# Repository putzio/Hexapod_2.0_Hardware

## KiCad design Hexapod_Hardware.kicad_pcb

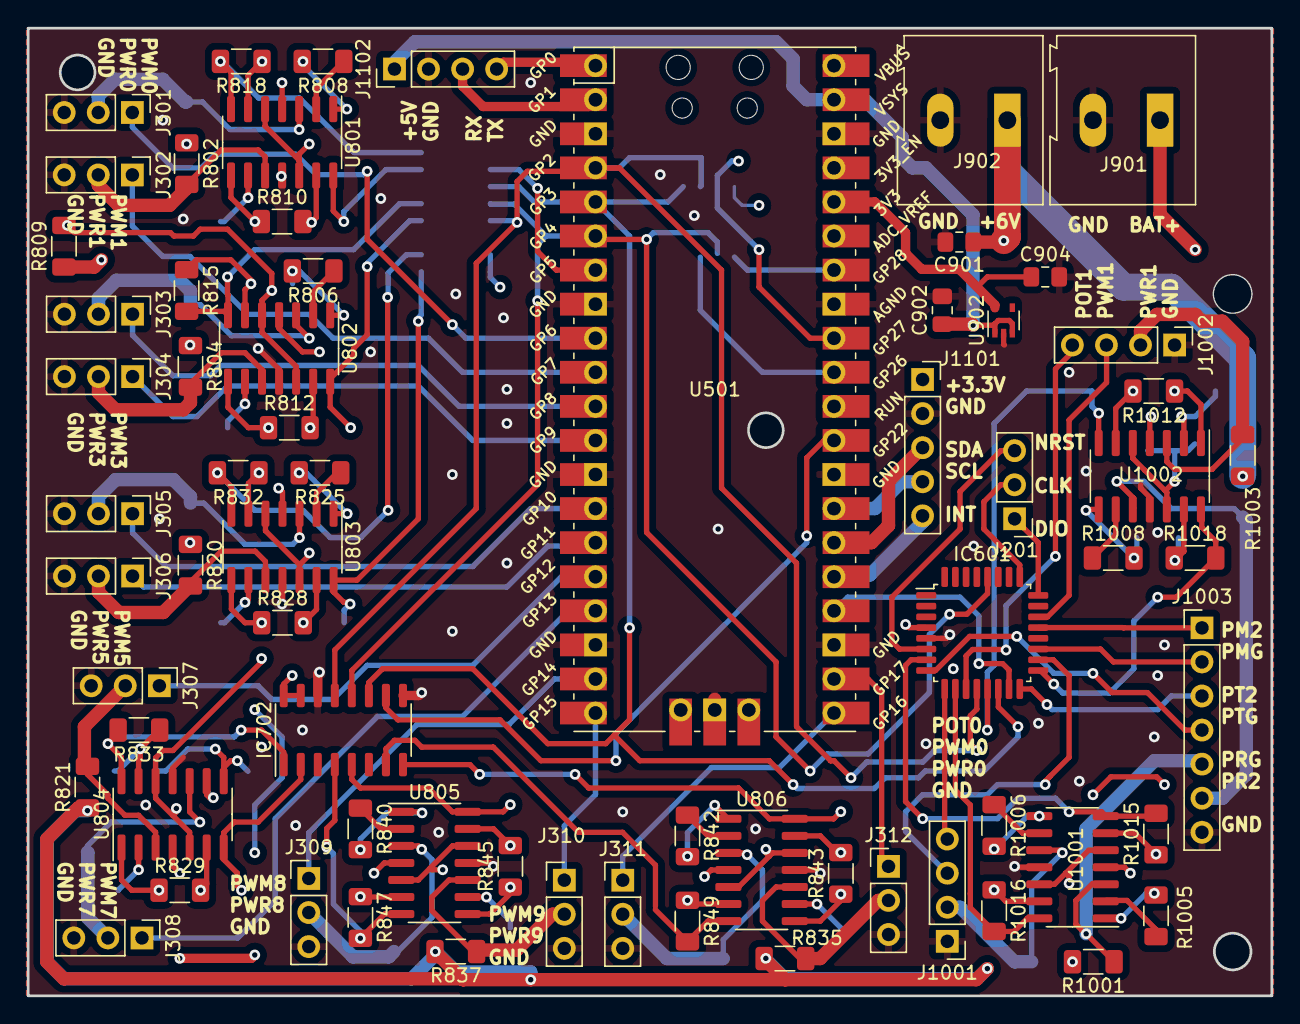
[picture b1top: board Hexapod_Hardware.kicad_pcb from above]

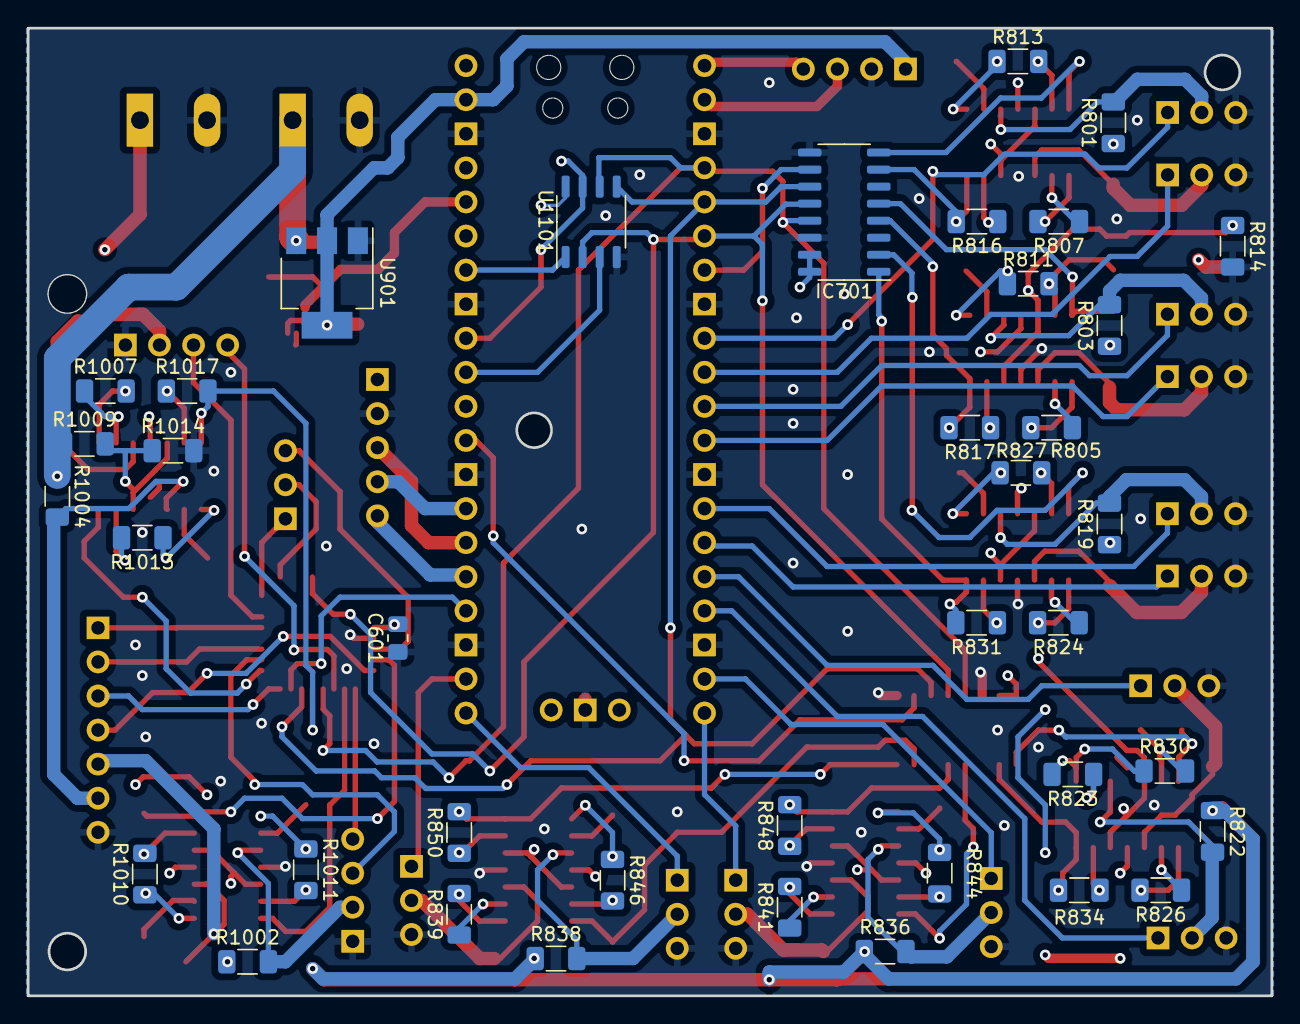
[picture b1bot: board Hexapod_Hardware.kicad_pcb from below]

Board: 4 copper layers, 92.7 x 72.1 mm, 107 parts (39 on the bottom side), 124 nets.

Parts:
C601: 10uF; C_0805_2012Metric_Pad1.18x1.45mm_HandSolder
C901, C902: 22uF; C_0805_2012Metric_Pad1.18x1.45mm_HandSolder
C904: 1uF; C_0805_2012Metric_Pad1.18x1.45mm_HandSolder
IC601: STM32G030K8T6; LQFP-32_7x7mm_P0.8mm
IC701, IC702: MCP3008-I_SL; SO-16_3.9x9.9mm_P1.27mm
J201: Conn_01x03; PinHeader_1x03_P2.54mm_Vertical
J301, J302, J303, J304, J305, J306, J307, J308, J309, J310, J311, J312: Conn_01x03_Female; PinHeader_1x03_P2.54mm_Vertical
J901, J902: Screw_Terminal_01x02; TerminalBlock_Altech_AK300-2_P5.00mm
J1001, J1002: Conn_01x04_Pin; PinHeader_1x04_P2.54mm_Vertical
J1003: Conn_01x07; PinHeader_1x07_P2.54mm_Vertical
J1101: Conn_01x05_Pin; PinSocket_1x05_P2.54mm_Vertical
J1102: Conn_01x04_Socket; PinHeader_1x04_P2.54mm_Vertical
R801: 0R39; R_1206_3216Metric_Pad1.30x1.75mm_HandSolder
R802, R803, R804, R805, R806, R807, R808, R819, R820, R821, R822, R823, R824, R825, R826, R835, R836, R837, R838, R839, R840, R842, R1001, R1002, R1003, R1004, R1005, R1006, R1007, R1008: R; R_1206_3216Metric_Pad1.30x1.75mm_HandSolder
R809, R810, R811, R812, R813, R827, R828, R829, R830, R843, R844, R845, R846, R1009, R1010, R1011, R1012, R1013: 10k; R_1206_3216Metric_Pad1.30x1.75mm_HandSolder
R814, R815, R816, R817, R818, R831, R832, R833, R834, R841, R847, R848, R849, R850, R1014, R1015, R1016, R1017, R1018: 47k; R_1206_3216Metric_Pad1.30x1.75mm_HandSolder
U501: Pico; RPi_Pico_SMD_TH
U801, U802, U803, U804, U805, U806, U1001, U1002: LM2902; SOIC-14_3.9x8.7mm_P1.27mm
U901: AZ1117CH-5.0TRG1; SOT-223-3_TabPin2
U902: LD29150DT33R; SOT-353_SC-70-5
U1101: AT25SF081-XMHD-X; SOP-8_3.9x4.9mm_P1.27mm

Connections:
+3.3V: C601.2, C904.1, IC601.4 (VDD/VDDA), IC701.15 (VREF), IC701.16 (VDD), IC702.15 (VREF), IC702.16 (VDD), J1101.1, U501.36 (3V3), U902.5 (VOUT), U1101.8 (VCC)
+5V: C902.1, J1102.1, U501.39 (VSYS), U901.2 (VO), U902.1 (VIN), U902.3 (EN)
+6V: C901.1, J902.1, R801.1, R802.1, R803.1, R804.1, R809.1, R819.1, R820.1, R821.1, R822.1, R835.1, R836.1, R837.1, R838.1, R1001.1, R1002.1, R1003.1, R1004.1, R1009.1, U901.3 (VI)
+8V: J901.1, U801.4 (V+), U802.4 (V+), U803.4 (V+), U804.4 (V+), U805.4 (V+), U806.4 (V+), U1001.4 (V+), U1002.4 (V+)
/MCU/FLASH_HOLD: U501.32 (GPIO27_ADC1), U1101.7 (~HOLD/IO3)
/MCU/FLASH_WP: U501.31 (GPIO26_ADC0), U1101.3 (~WP/IO2)
/MCU/I2C_SCL: J1101.4, U501.27 (GPIO21)
/MCU/I2C_SDA: J1101.3, U501.26 (GPIO20)
/MCU/MPU6050_INT: J1101.5, U501.25 (GPIO19)
/MCU/RX: J1102.3, U501.2 (GPIO1)
/MCU/SERVO_0: J301.1, U501.9 (GPIO6)
/MCU/SERVO_1: J302.1, U501.10 (GPIO7)
/MCU/SERVO_2: J303.1, U501.11 (GPIO8)
/MCU/SERVO_3: J304.1, U501.12 (GPIO9)
/MCU/SERVO_4: J305.1, U501.14 (GPIO10)
/MCU/SERVO_5: J306.1, U501.15 (GPIO11)
/MCU/SERVO_6: J307.1, U501.16 (GPIO12)
/MCU/SERVO_7: J308.1, U501.17 (GPIO13)
/MCU/SERVO_8: J309.1, U501.19 (GPIO14)
/MCU/SERVO_9: J310.1, U501.20 (GPIO15)
/MCU/SERVO_10: J311.1, U501.21 (GPIO16)
/MCU/SERVO_11: J312.1, U501.22 (GPIO17)
/MCU/SPI_CLK: IC601.12 (PA5), IC701.13 (CLK), IC702.13 (CLK), U501.4 (GPIO2), U1101.6 (SCK)
/MCU/SPI_CS_0: IC701.10 (~CS/SHDN), U501.7 (GPIO5)
/MCU/SPI_CS_1: IC702.10 (~CS/SHDN), U501.29 (GPIO22)
/MCU/SPI_CS_2: U501.34 (GPIO28_ADC2), U1101.1 (~CS)
/MCU/SPI_CS_GRIPPER: IC601.15 (PB0), U501.24 (GPIO18)
/MCU/SPI_MISO: IC601.28 (PB4), IC701.12 (DOUT), IC702.12 (DOUT), U501.6 (GPIO4), U1101.2 (SO/IO1)
/MCU/SPI_MOSI: IC601.14 (PA7), IC701.11 (DIN), IC702.11 (DIN), U501.5 (GPIO3), U1101.5 (SI/IO0)
/MCU/TX: J1102.4, U501.1 (GPIO0)
/SERVO + ADC/ADC/CURRENT_SENSOR_0: IC701.8 (CH7), R818.2, U801.7
/SERVO + ADC/ADC/CURRENT_SENSOR_1: IC701.7 (CH6), R816.2, U801.14
/SERVO + ADC/ADC/CURRENT_SENSOR_2: IC701.5 (CH4), R815.2, U802.7
/SERVO + ADC/ADC/CURRENT_SENSOR_3: IC701.4 (CH3), R817.2, U802.14
/SERVO + ADC/ADC/CURRENT_SENSOR_4: IC701.2 (CH1), R832.2, U803.7
/SERVO + ADC/ADC/CURRENT_SENSOR_5: IC701.1 (CH0), R831.2, U803.14
/SERVO + ADC/ADC/CURRENT_SENSOR_6: IC702.2 (CH1), R834.2, U804.7
/SERVO + ADC/ADC/CURRENT_SENSOR_7: IC702.1 (CH0), R833.2, U804.14
/SERVO + ADC/ADC/CURRENT_SENSOR_8: IC702.4 (CH3), R847.2, U805.7
/SERVO + ADC/ADC/CURRENT_SENSOR_9: IC702.5 (CH4), R848.2, U805.14
/SERVO + ADC/ADC/CURRENT_SENSOR_10: IC702.7 (CH6), R849.2, U806.7
/SERVO + ADC/ADC/CURRENT_SENSOR_11: IC702.8 (CH7), R850.2, U806.14
/SERVO + ADC/Current Sensors/SERVO_PWR_0: J301.2, R801.2, U801.3 (+)
/SERVO + ADC/Current Sensors/SERVO_PWR_1: J302.2, R802.2, U801.10 (+)
/SERVO + ADC/Current Sensors/SERVO_PWR_2: J303.2, R803.2, U802.3 (+)
/SERVO + ADC/Current Sensors/SERVO_PWR_3: J304.2, R804.2, U802.10 (+)
/SERVO + ADC/Current Sensors/SERVO_PWR_4: J305.2, R819.2, U803.3 (+)
/SERVO + ADC/Current Sensors/SERVO_PWR_5: J306.2, R820.2, U803.10 (+)
/SERVO + ADC/Current Sensors/SERVO_PWR_6: J307.2, R821.2, U804.3 (+)
/SERVO + ADC/Current Sensors/SERVO_PWR_7: J308.2, R822.2, U804.10 (+)
/SERVO + ADC/Current Sensors/SERVO_PWR_8: J309.2, R836.2, U805.3 (+)
/SERVO + ADC/Current Sensors/SERVO_PWR_9: J310.2, R837.2, U805.10 (+)
/SERVO + ADC/Current Sensors/SERVO_PWR_10: J311.2, R838.2, U806.3 (+)
/SERVO + ADC/Current Sensors/SERVO_PWR_11: J312.2, R835.2, U806.10 (+)
/SERVO + ADC/Current Sensors/V_BAT_REF: R809.2, R814.1, U801.5 (+), U801.12 (+), U802.5 (+), U802.12 (+), U803.5 (+), U803.12 (+), U804.5 (+), U804.12 (+), U805.5 (+), U805.12 (+), U806.5 (+), U806.12 (+)
/SUPPORTING_MODULES/Gripper/Gripper_servo/SERVO_0_CURRENT: IC601.10 (PA3), R1016.2, U1001.14
/SUPPORTING_MODULES/Gripper/Gripper_servo/SERVO_1_CURRENT: IC601.13 (PA6), R1017.2, U1002.7
/SUPPORTING_MODULES/Gripper/Gripper_servo/SERVO_2_CURRENT: IC601.17 (PB2), R1018.2, U1002.14
/SUPPORTING_MODULES/Gripper/Gripper_servo/SERVO_CURRENT_GRIPPER: IC601.7 (PA0), R1015.2, U1001.7
/SUPPORTING_MODULES/Gripper/Gripper_servo/SERVO_POTENTIOMETER_0: IC601.9 (PA2), J1001.4
/SUPPORTING_MODULES/Gripper/Gripper_servo/SERVO_POTENTIOMETER_1: IC601.11 (PA4), J1002.4
/SUPPORTING_MODULES/Gripper/Gripper_servo/SERVO_POTENTIOMETER_2: IC601.16 (PB1), J1003.3
/SUPPORTING_MODULES/Gripper/Gripper_servo/SERVO_POTENTIOMETER_GRIPPER: IC601.8 (PA1), J1003.4
/SUPPORTING_MODULES/Gripper/Gripper_servo/SERVO_PWM_0: IC601.18 (PA8), J1001.3
/SUPPORTING_MODULES/Gripper/Gripper_servo/SERVO_PWM_1: IC601.22 (PA11_[PA9]), J1002.3
/SUPPORTING_MODULES/Gripper/Gripper_servo/SERVO_PWM_2: IC601.21 (PA10), J1003.1
/SUPPORTING_MODULES/Gripper/Gripper_servo/SERVO_PWM_GRIPPER: IC601.19 (PA9), J1003.2
/SUPPORTING_MODULES/Gripper/Gripper_servo/SERVO_PWR_0: J1001.2, R1002.2, U1001.10 (+)
/SUPPORTING_MODULES/Gripper/Gripper_servo/SERVO_PWR_1: J1002.2, R1003.2, U1002.3 (+)
/SUPPORTING_MODULES/Gripper/Gripper_servo/SERVO_PWR_2: J1003.6, R1004.2, U1002.10 (+)
/SUPPORTING_MODULES/Gripper/Gripper_servo/SERVO_PWR_GRIPPER: J1003.5, R1001.2, U1001.3 (+)
/SUPPORTING_MODULES/Gripper/Gripper_servo/V_BAT_REF: R1009.2, R1014.1, U1001.5 (+), U1001.12 (+), U1002.5 (+), U1002.12 (+)
/SUPPORTING_MODULES/Gripper/MCU_GRIPPER/NRST: IC601.6 (NRST), J201.3
/SUPPORTING_MODULES/Gripper/MCU_GRIPPER/SWCLK: IC601.25 (PA14-BOOT0), J201.2
/SUPPORTING_MODULES/Gripper/MCU_GRIPPER/SWDIO: IC601.24 (PA13), J201.1
GND: C601.1, C901.2, C902.2, C904.2, IC601.5 (VSS/VSSA), IC701.9 (DGND), IC701.14 (AGND), IC702.9 (DGND), IC702.14 (AGND), J301.3, J302.3, J303.3, J304.3, J305.3, J306.3, J307.3, J308.3, J309.3, J310.3, J311.3, J312.3, J901.2, J902.2, J1001.1, J1002.1, J1003.7, J1101.2, J1102.2, R814.2, R1014.2, U501.3 (GND), U501.8 (GND), U501.13 (GND), U501.18 (GND), U501.23 (GND), U501.28 (GND), U501.33 (AGND), U501.38 (GND), U501.42 (GND), U801.11 (V-), U802.11 (V-), U803.11 (V-), U804.11 (V-), U805.11 (V-), U806.11 (V-), U901.1 (ADJ), U902.2 (GND), U1001.11 (V-), U1002.11 (V-), U1101.4 (GND)
unnamed: R805.2, R812.1, U802.8
unnamed: R806.2, R811.1, U802.1
unnamed: R807.2, R810.1, U801.8
unnamed: R808.2, R813.1, U801.1
unnamed: R823.2, R830.1, U804.8
unnamed: R824.2, R828.1, U803.8
unnamed: R825.2, R827.1, U803.1
unnamed: R826.2, R829.1, U804.1
unnamed: R839.2, R843.1, U806.8
unnamed: R840.2, R844.1, U805.1
unnamed: R841.2, R845.1, U805.8
unnamed: R842.2, R846.1, U806.1
unnamed: R1005.2, R1010.1, U1001.1
unnamed: R1006.2, R1011.1, U1001.8
unnamed: R1007.2, R1012.1, U1002.1
unnamed: R1008.2, R1013.1, U1002.8
unnamed: R808.1, U801.2 (-)
unnamed: R813.2, R818.1, U801.6 (-)
unnamed: R807.1, U801.9 (-)
unnamed: R810.2, R816.1, U801.13 (-)
unnamed: R806.1, U802.2 (-)
unnamed: R811.2, R815.1, U802.6 (-)
unnamed: R805.1, U802.9 (-)
unnamed: R812.2, R817.1, U802.13 (-)
unnamed: R825.1, U803.2 (-)
unnamed: R827.2, R832.1, U803.6 (-)
unnamed: R824.1, U803.9 (-)
unnamed: R828.2, R831.1, U803.13 (-)
unnamed: R826.1, U804.2 (-)
unnamed: R829.2, R834.1, U804.6 (-)
unnamed: R823.1, U804.9 (-)
unnamed: R830.2, R833.1, U804.13 (-)
unnamed: R840.1, U805.2 (-)
unnamed: R844.2, R847.1, U805.6 (-)
unnamed: R841.1, U805.9 (-)
unnamed: R845.2, R848.1, U805.13 (-)
unnamed: R842.1, U806.2 (-)
unnamed: R846.2, R849.1, U806.6 (-)
unnamed: R839.1, U806.9 (-)
unnamed: R843.2, R850.1, U806.13 (-)
unnamed: R1005.1, U1001.2 (-)
unnamed: R1010.2, R1015.1, U1001.6 (-)
unnamed: R1006.1, U1001.9 (-)
unnamed: R1011.2, R1016.1, U1001.13 (-)
unnamed: R1007.1, U1002.2 (-)
unnamed: R1012.2, R1017.1, U1002.6 (-)
unnamed: R1008.1, U1002.9 (-)
unnamed: R1013.2, R1018.1, U1002.13 (-)

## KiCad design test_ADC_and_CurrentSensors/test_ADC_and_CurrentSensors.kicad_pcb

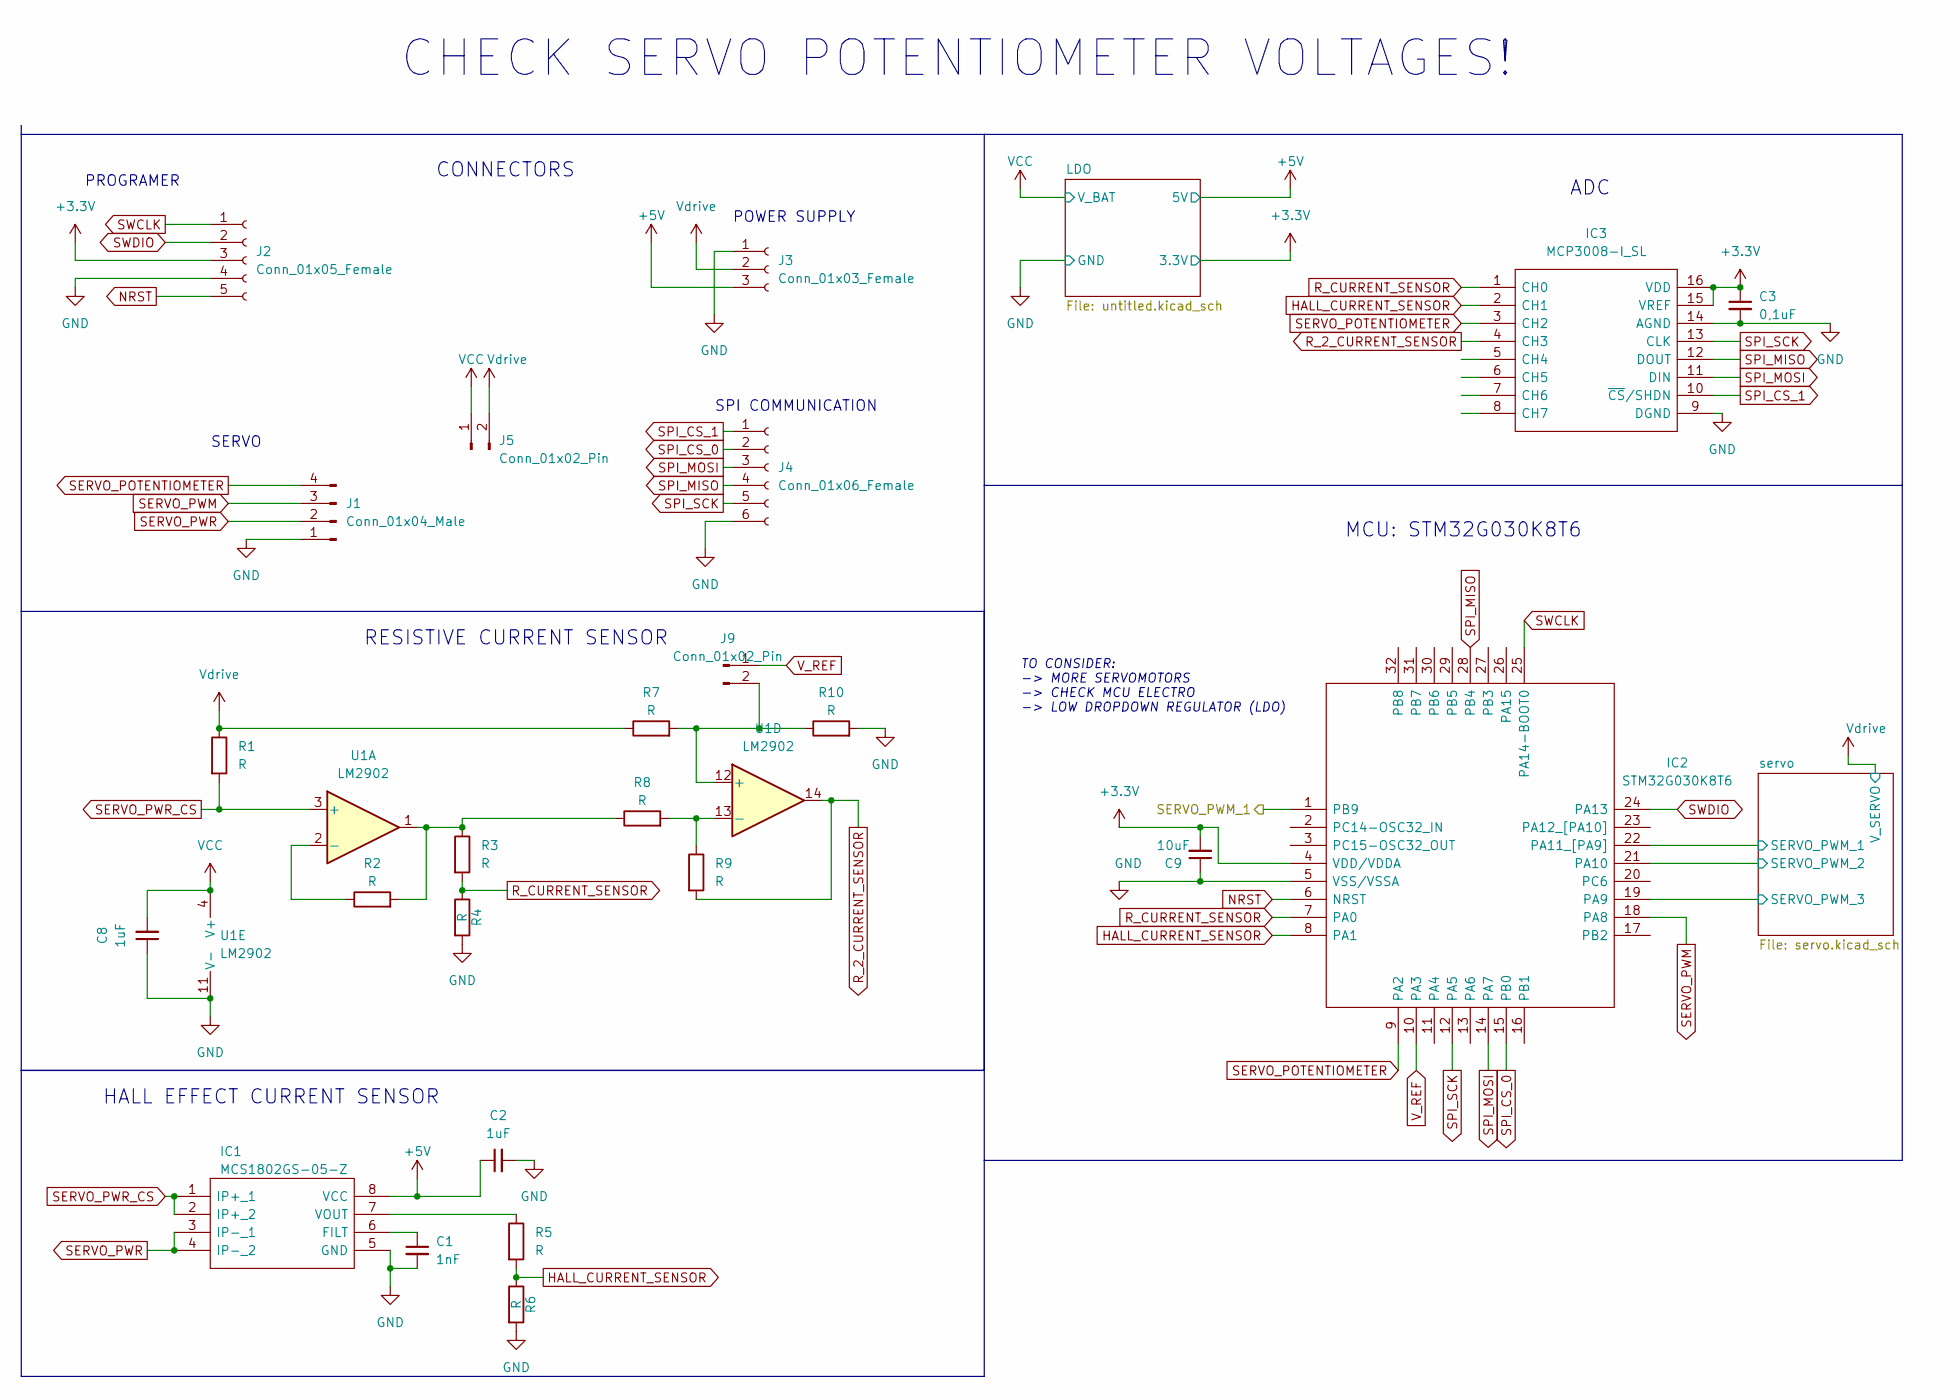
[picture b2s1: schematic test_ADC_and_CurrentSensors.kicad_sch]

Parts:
C1: 1nF; C_0805_2012Metric_Pad1.18x1.45mm_HandSolder
C2, C8: 1uF; C_0805_2012Metric_Pad1.18x1.45mm_HandSolder
C3: 0,1uF; C_0805_2012Metric_Pad1.18x1.45mm_HandSolder
C9: 10uF; C_0805_2012Metric_Pad1.18x1.45mm_HandSolder
IC1: MCS1802GS-05-Z; SOIC-8_5.275x5.275mm_P1.27mm; Manufacturer_Part_Number MCS1802GS-05-Z; Mouser Part Number 946-MCS1802GS-05-Z
IC2: STM32G030K8T6; LQFP-32_7x7mm_P0.8mm; Manufacturer_Part_Number STM32G030K8T6; Mouser Part Number 511-STM32G030K8T6
IC3: MCP3008-I_SL; SOIC-16_3.9x9.9mm_P1.27mm; Manufacturer_Part_Number MCP3008-I/SL; Mouser Part Number 579-MCP3008-I/SL
J1: Conn_01x04_Male; PinHeader_1x04_P2.54mm_Vertical
J2: Conn_01x05_Female; PinSocket_1x05_P2.54mm_Vertical
J3: Conn_01x03_Female; PinSocket_1x03_P2.54mm_Vertical
J4: Conn_01x06_Female; PinSocket_1x06_P2.54mm_Vertical
J5, J9: Conn_01x02_Pin; PinHeader_1x02_P2.54mm_Vertical
R1, R2, R3, R4, R5, R6, R9, R10: R; R_1206_3216Metric
R7, R8: R; R_Axial_DIN0204_L3.6mm_D1.6mm_P7.62mm_Horizontal
U1: LM2902; SOIC-14_3.9x8.7mm_P1.27mm

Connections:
+3.3V: C3.1, C9.2, IC2.4 (VDD/VDDA), IC3.15 (VREF), IC3.16 (VDD), J2.3; also elsewhere on the board
+5V: C2.1, IC1.8 (VCC), J3.3; also elsewhere on the board
/SERVO_PWM_1: IC2.1 (PB9)
/servo/SERVO_PWM_1: IC2.22 (PA11_[PA9]); also elsewhere on the board
/servo/SERVO_PWM_2: IC2.21 (PA10); also elsewhere on the board
/servo/SERVO_PWM_3: IC2.19 (PA9); also elsewhere on the board
GND: C1.2, C2.2, C3.2, C8.1, C9.1, IC1.5 (GND), IC2.5 (VSS/VSSA), IC3.9 (DGND), IC3.14 (AGND), J1.1, J2.4, J3.1, J4.6, R4.2, R6.2, R10.2, U1.11 (V-); also elsewhere on the board
HALL_CURRENT_SENSOR: IC2.8 (PA1), IC3.2 (CH1), R5.2, R6.1
NRST: IC2.6 (NRST), J2.5
unnamed: C1.1, IC1.6 (FILT)
unnamed: IC1.7 (VOUT), R5.1
unnamed: J9.2, R7.2, R10.1, U1.12 (+)
unnamed: R2.2, R3.1, R8.1, U1.1
unnamed: R2.1, U1.2 (-)
unnamed: R8.2, R9.1, U1.13 (-)
R_2_CURRENT_SENSOR: IC3.4 (CH3), R9.2, U1.14
R_CURRENT_SENSOR: IC2.7 (PA0), IC3.1 (CH0), R3.2, R4.1
SERVO_POTENTIOMETER: IC2.9 (PA2), IC3.3 (CH2), J1.4
SERVO_PWM: IC2.18 (PA8), J1.3
SERVO_PWR: IC1.3 (IP-_1), IC1.4 (IP-_2), J1.2
SERVO_PWR_CS: IC1.1 (IP+_1), IC1.2 (IP+_2), R1.2, U1.3 (+)
SPI_CS_0: IC2.15 (PB0), J4.2
SPI_CS_1: IC3.10 (~CS/SHDN), J4.1
SPI_MISO: IC2.28 (PB4), IC3.12 (DOUT), J4.4
SPI_MOSI: IC2.14 (PA7), IC3.11 (DIN), J4.3
SPI_SCK: IC2.12 (PA5), IC3.13 (CLK), J4.5
SWCLK: IC2.25 (PA14-BOOT0), J2.1
SWDIO: IC2.24 (PA13), J2.2
VCC: C8.2, J5.1, U1.4 (V+); also elsewhere on the board
V_REF: IC2.10 (PA3), J9.1
Vdrive: J3.2, J5.2, R1.1, R7.1; also elsewhere on the board

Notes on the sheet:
HALL EFFECT CURRENT SENSOR
POWER SUPPLY
MCU: STM32G030K8T6
SERVO
RESISTIVE CURRENT SENSOR
PROGRAMER
ADC
TO CONSIDER: -> MORE SERVOMOTORS -> CHECK MCU ELECTRO -> LOW DROPDOWN REGULATOR (LDO)
CHECK SERVO POTENTIOMETER VOLTAGES!
SPI COMMUNICATION
CONNECTORS

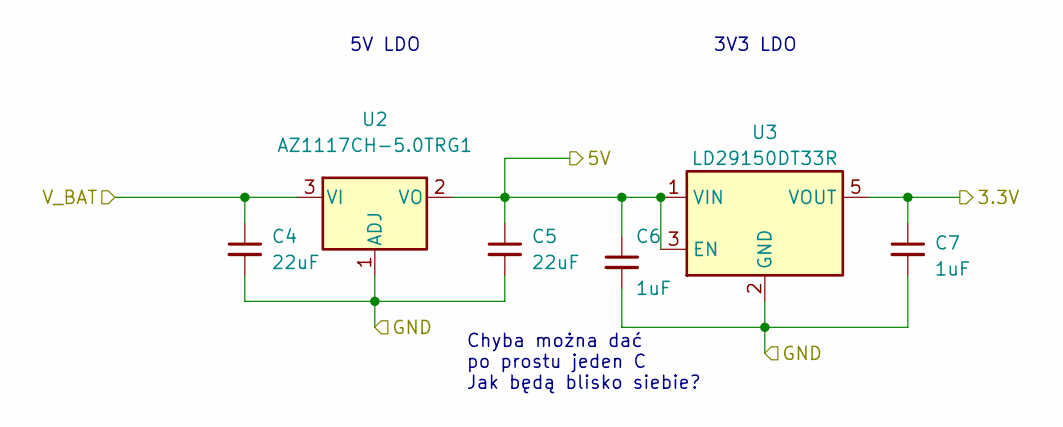
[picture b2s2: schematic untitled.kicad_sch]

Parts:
C4, C5: 22uF; C_0805_2012Metric_Pad1.18x1.45mm_HandSolder
C6, C7: 1uF; C_0805_2012Metric_Pad1.18x1.45mm_HandSolder
U2: AZ1117CH-5.0TRG1; SOT-223-3_TabPin2
U3: LD29150DT33R; SOT-353_SC-70-5

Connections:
+3.3V: C7.1, U3.5 (VOUT); also elsewhere on the board
+5V: C5.1, C6.1, U2.2 (VO), U3.1 (VIN), U3.3 (EN); also elsewhere on the board
GND: C4.2, C5.2, C6.2, C7.2, U2.1 (ADJ), U3.2 (GND); also elsewhere on the board
VCC: C4.1, U2.3 (VI); also elsewhere on the board

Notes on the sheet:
5V LDO
Chyba można dać po prostu jeden C Jak będą blisko siebie?
3V3 LDO

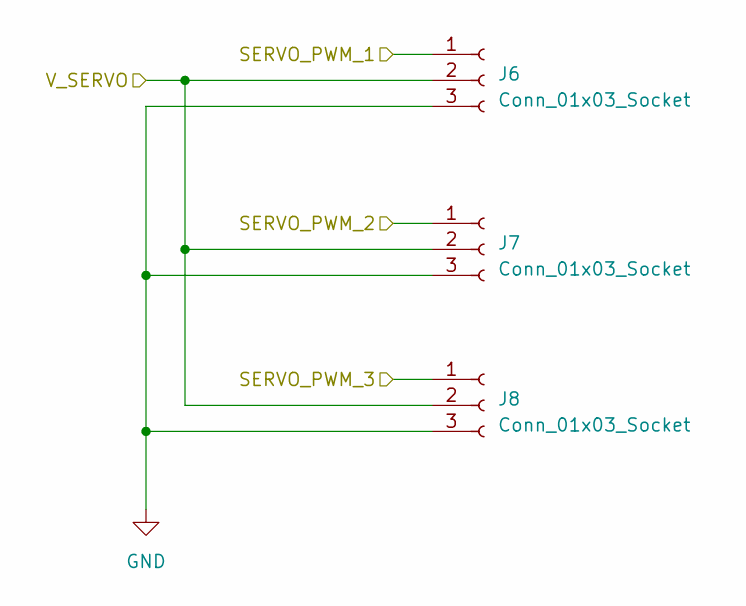
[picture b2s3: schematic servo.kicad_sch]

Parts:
J6, J7, J8: Conn_01x03_Socket; PinSocket_1x03_P2.54mm_Vertical

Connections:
/servo/SERVO_PWM_1: J6.1; also elsewhere on the board
/servo/SERVO_PWM_2: J7.1; also elsewhere on the board
/servo/SERVO_PWM_3: J8.1; also elsewhere on the board
GND: J6.3, J7.3, J8.3; also elsewhere on the board
Vdrive: J6.2, J7.2, J8.2; also elsewhere on the board

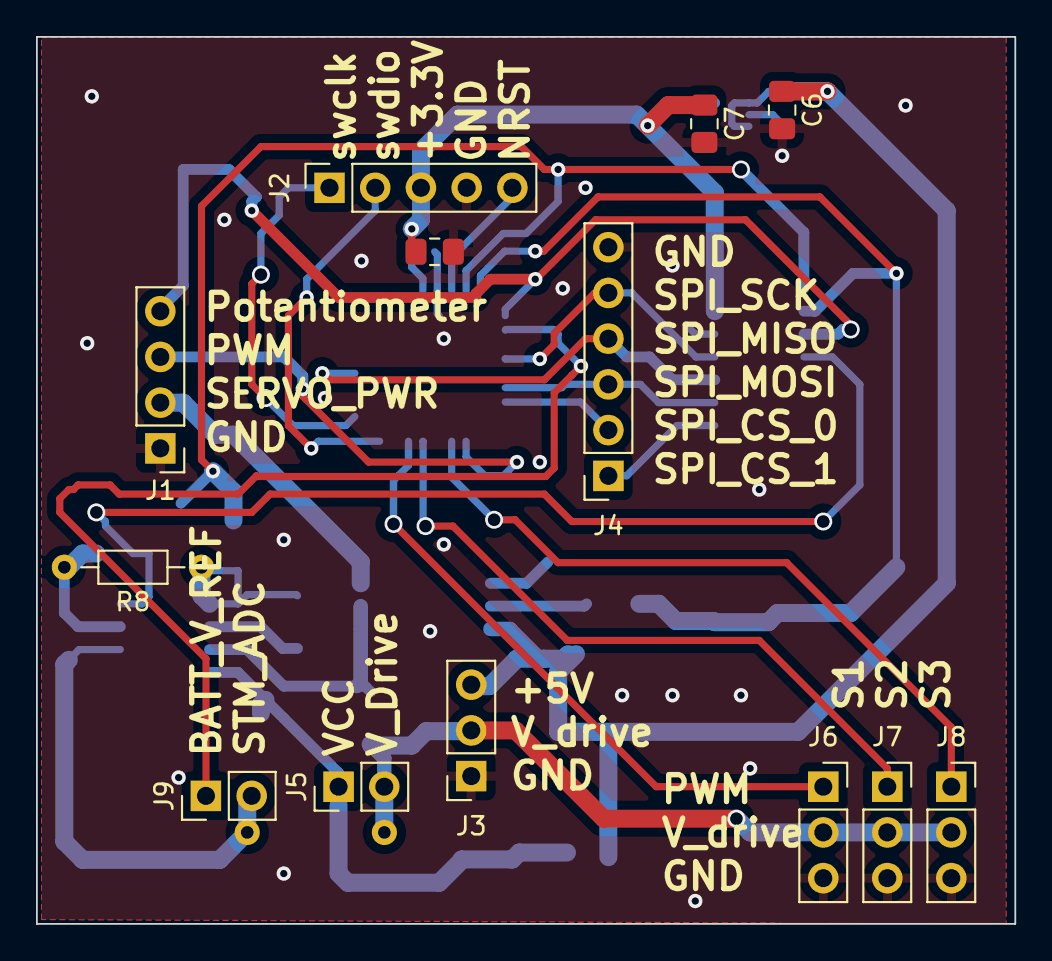
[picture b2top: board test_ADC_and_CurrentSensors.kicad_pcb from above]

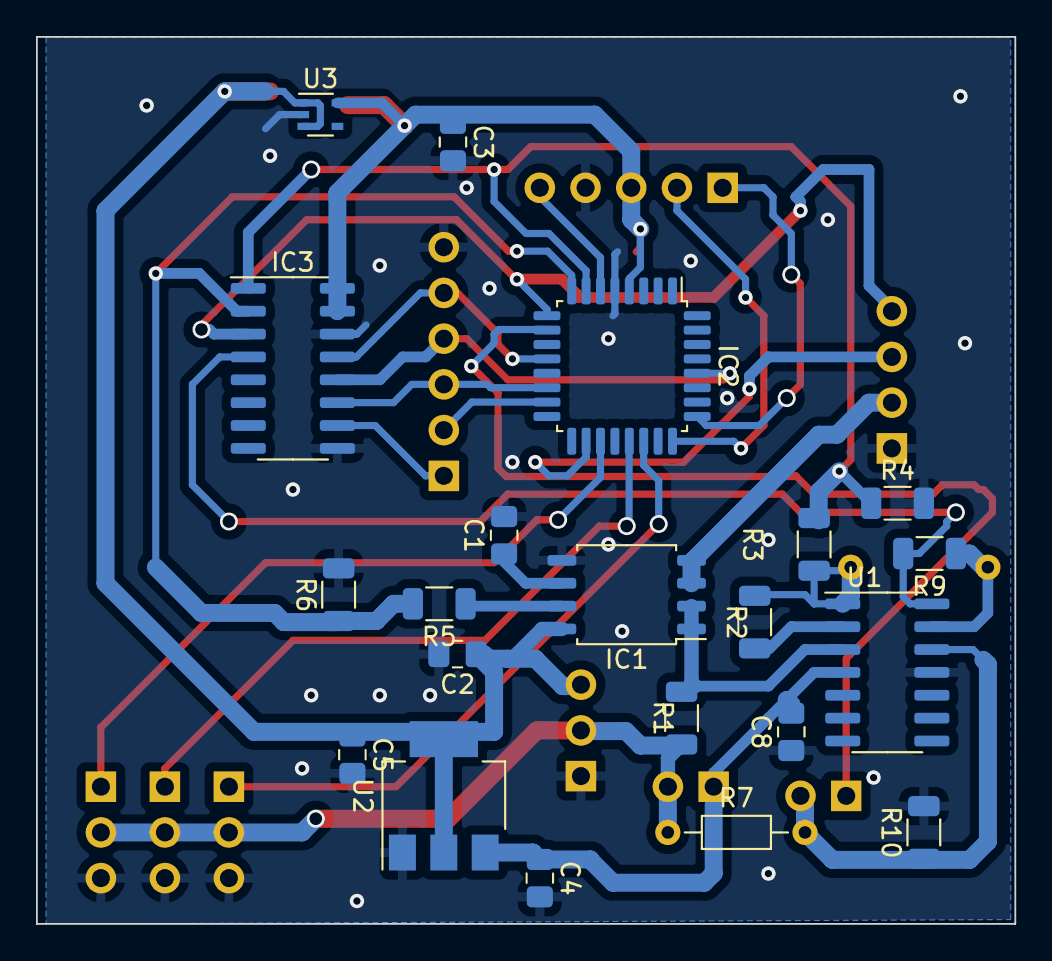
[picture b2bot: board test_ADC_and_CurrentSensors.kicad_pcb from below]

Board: 2 copper layers, 54.4 x 49.3 mm, 34 parts (21 on the bottom side), 30 nets.

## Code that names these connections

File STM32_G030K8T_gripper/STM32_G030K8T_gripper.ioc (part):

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Mcu.Name=STM32G030K(6-8)Tx
Mcu.Package=LQFP32
Mcu.UserName=STM32G030K8Tx
PA0.Mode=IN0
PA0.Signal=ADC1_IN0
PA1.Mode=IN1
PA1.Signal=ADC1_IN1
PA10.Signal=S_TIM1_CH3
PA11\ [PA9].Signal=S_TIM1_CH4
PA13.Mode=Serial_Wire
PA13.Signal=SYS_SWDIO
PA14-BOOT0.Mode=Serial_Wire
PA14-BOOT0.Signal=SYS_SWCLK
PA2.Mode=IN2
PA2.Signal=ADC1_IN2
PA3.Mode=IN3
PA3.Signal=ADC1_IN3
PA4.Mode=IN4
PA4.Signal=ADC1_IN4
PA5.Mode=Full_Duplex_Slave
PA5.Signal=SPI1_SCK
PA6.Mode=IN6
PA6.Signal=ADC1_IN6
PA7.Mode=Full_Duplex_Slave
PA7.Signal=SPI1_MOSI
PA8.Signal=S_TIM1_CH1
PA9.Signal=S_TIM1_CH2
PB0.Mode=NSS_Signal_Hard_Input
PB0.Signal=SPI1_NSS
PB1.Mode=IN9
PB1.Signal=ADC1_IN9
PB2.Mode=IN10
PB2.Signal=ADC1_IN10
PB4.Mode=Full_Duplex_Slave
PB4.Signal=SPI1_MISO
PC6.Signal=S_TIM3_CH1
RCC.HSE_VALUE=8000000
RCC.SYSCLKFreq_VALUE=16000000
board=custom

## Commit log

2023-04-28 Finished PCB
2023-04-28 CUBE_MX .ioc project to generate init code for the gripper
2023-04-28 Added testing board + fixed gerber files
2023-04-29 new gerber files for hexapod
2023-05-25 cleaning up
2023-07-01 ordered pcbs
2023-07-06 Bord v1.2, added flash memory, changed pinout od servomotor connectors and removed potentiometer signal from servomotors plus one ADC
2023-07-12 new pcb
